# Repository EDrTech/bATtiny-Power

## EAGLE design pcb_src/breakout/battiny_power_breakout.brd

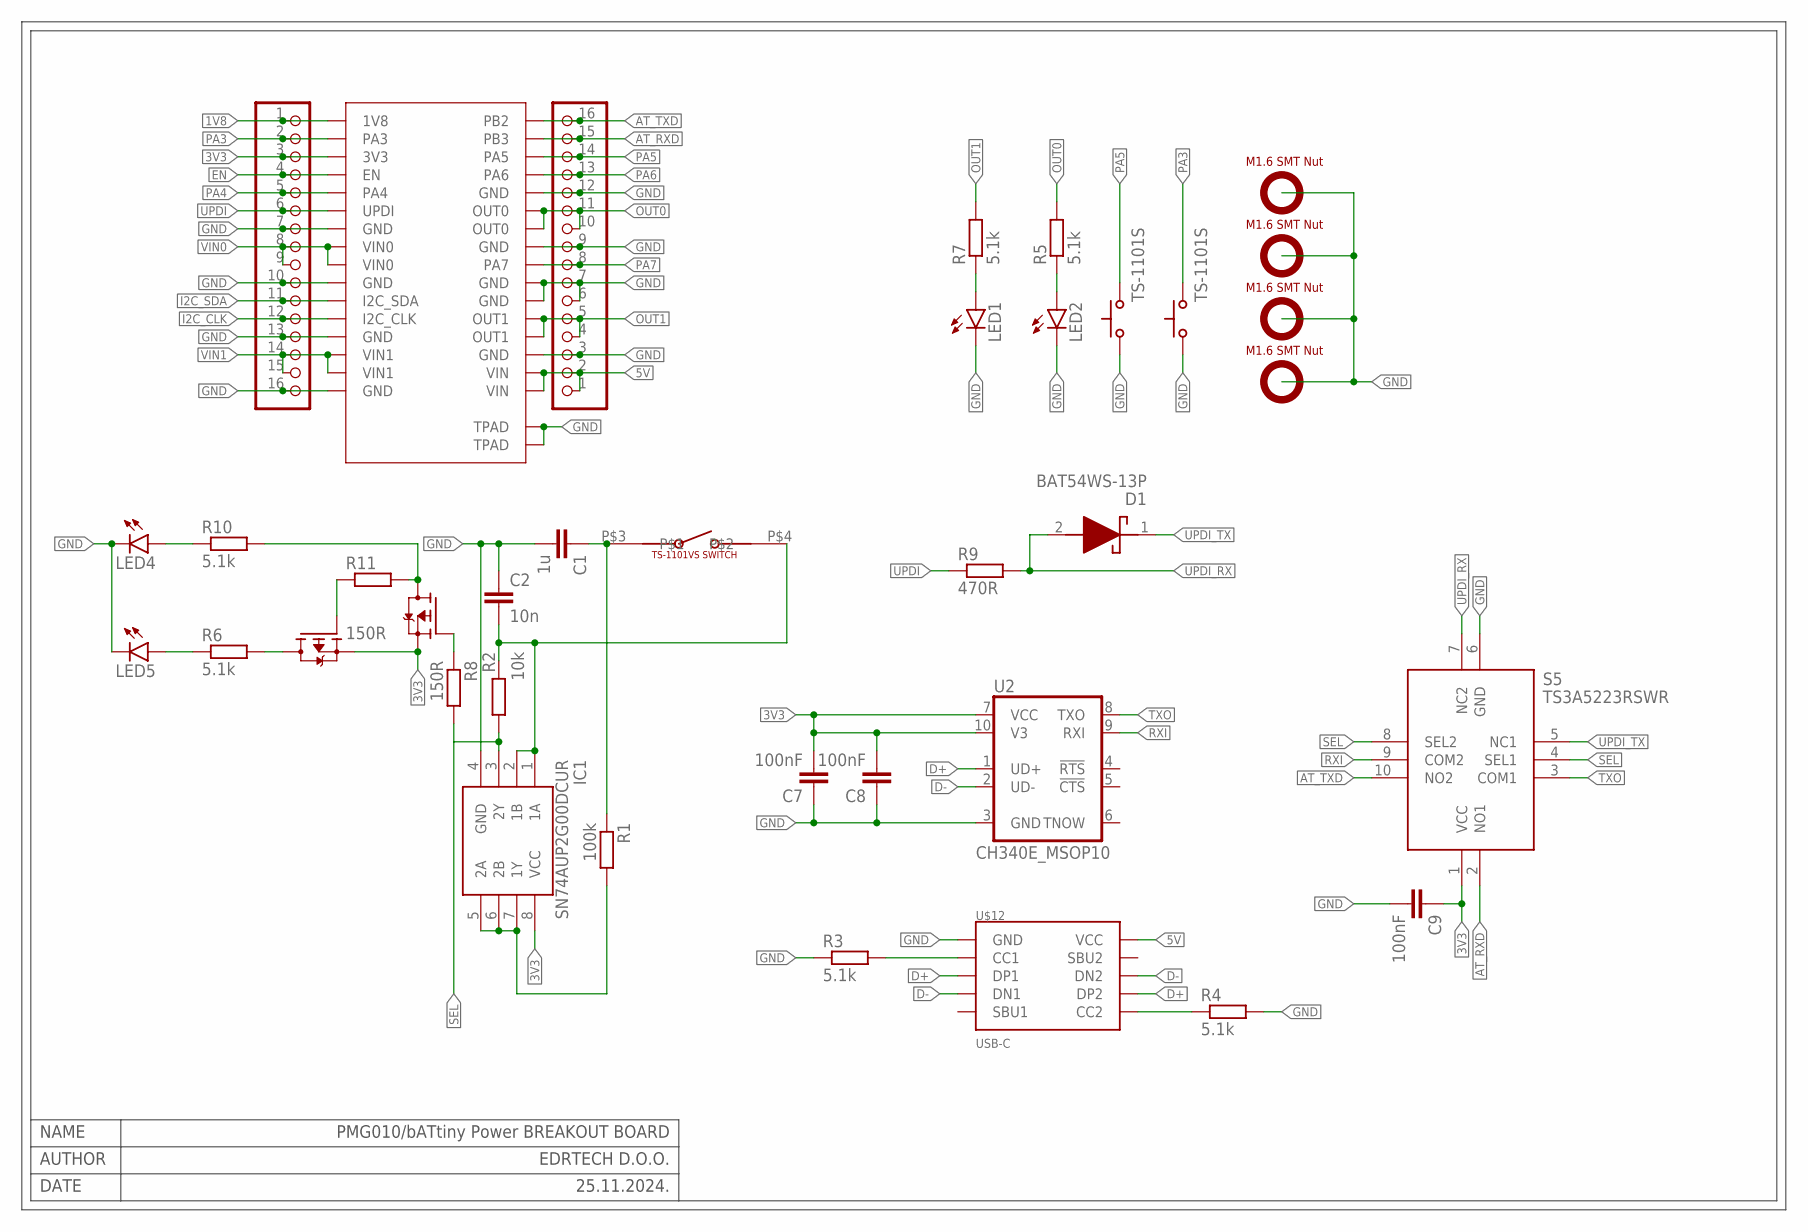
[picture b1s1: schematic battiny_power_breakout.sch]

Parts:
C1: 1u; C0402
C2: 10n; C0402
C7, C8, C9: 100nF; C0402
D1: BAT54WS-13P; SOD2512X115N
IC1: SN74AUP2G00DCUR; SOP50P310X90-8N
JP1, JP2: PINHD-1X16; 1X16
LED1, LED2, LED4, LED5: LEDCHIP-LED0603; CHIP-LED0603
Q1, Q2: NTK3139PT1G; SOTFL40P120X55-3N
R1: 100k; R0402
R2: 10k; R0402
R3, R4, R5, R6, R7, R10: 5.1k; R0402
R8, R11: 150R; R0402
R9: 470R; R0402
S5: TS3A5223RSWR; RSW(RPUQFNN10)
U2: CH340E_MSOP10; MSOP10
U$1, U$4: TS-1101S
U$2: TS-1101VS-C-A-A
U$3: PMG010
U$8, U$9, U$10, U$11: SMTSO16
U$12: USB-C

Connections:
1V8: JP1.1, U$3.P$1 (1V8)
3V3: C7.2, C8.2, C9.1, IC1.8 (VCC), JP1.3, Q1.2 (S), Q2.2 (S), S5.1 (VCC), U2.7 (VCC), U2.10 (V3), U$3.P$3 (3V3)
5V: JP2.1, JP2.2, U$3.P$17 (VIN), U$3.P$18 (VIN), U$12.VCC@1 (VCC), U$12.VCC@2 (VCC)
AT_RXD: JP2.15, S5.2 (NO1), U$3.P$31 (PB3)
AT_TXD: JP2.16, S5.10 (NO2), U$3.P$32 (PB2)
D+: U2.1 (UD+), U$12.DP1, U$12.DP2
D-: U2.2 (UD-), U$12.DN1, U$12.DN2
EN: JP1.4, U$3.P$4 (EN)
GND: C1.2, C2.1, C7.1, C8.1, C9.2, IC1.4 (GND), JP1.7, JP1.10, JP1.13, JP1.16, JP2.3, JP2.6, JP2.7, JP2.9, JP2.12, LED1.C, LED2.C, LED4.C, LED5.C, R3.1, R4.2, S5.6 (GND), U2.3 (GND), U$1.P$1 (1), U$3.P$7 (GND), U$3.P$10 (GND), U$3.P$13 (GND), U$3.P$16 (GND), U$3.P$19 (GND), U$3.P$22 (GND), U$3.P$23 (GND), U$3.P$25 (GND), U$3.P$28 (GND), U$3.P$33 (TPAD), U$3.P$34 (TPAD), U$4.P$1 (1), U$8.P$1, U$9.P$1, U$10.P$1, U$11.P$1, U$12.GND@1 (GND), U$12.GND@2 (GND), U$12.P$1 (GND), U$12.P$2 (GND), U$12.P$3 (GND), U$12.P$4 (GND)
I2C_CLK: JP1.12, U$3.P$12 (I2C_CLK)
I2C_SDA: JP1.11, U$3.P$11 (I2C_SDA)
unnamed: C2.2, IC1.1 (1A), IC1.2 (1B), R2.1, U$2.P$4
unnamed: R3.2, U$12.CC1
unnamed: LED2.A, R5.1
unnamed: LED5.A, R6.1
unnamed: Q1.1 (G), R8.1
unnamed: R4.1, U$12.CC2
unnamed: IC1.5 (2A), IC1.6 (2B), IC1.7 (1Y), R1.2
unnamed: Q1.3 (D), R10.2, R11.2
unnamed: Q2.3 (D), R6.2
unnamed: LED4.A, R10.1
unnamed: C1.1, R1.1, U$2.P$3
unnamed: Q2.1 (G), R11.1
unnamed: LED1.A, R7.1
OUT0: JP2.10, JP2.11, R5.2, U$3.P$26 (OUT0), U$3.P$27 (OUT0)
OUT1: JP2.4, JP2.5, R7.2, U$3.P$20 (OUT1), U$3.P$21 (OUT1)
PA3: JP1.2, U$3.P$2 (PA3), U$4.P$2 (2)
PA4: JP1.5, U$3.P$5 (PA4)
PA5: JP2.14, U$1.P$2 (2), U$3.P$30 (PA5)
PA6: JP2.13, U$3.P$29 (PA6)
PA7: JP2.8, U$3.P$24 (PA7)
RXI: S5.9 (COM2), U2.9 (RXI)
SEL: IC1.3 (2Y), R2.2, R8.2, S5.4 (SEL1), S5.8 (SEL2)
TXO: S5.3 (COM1), U2.8 (TXO)
UPDI: JP1.6, R9.1, U$3.P$6 (UPDI)
UPDI_RX: D1.2 (A), R9.2, S5.7 (NC2)
UPDI_TX: D1.1 (K), S5.5 (NC1)
VIN0: JP1.8, JP1.9, U$3.P$8 (VIN0), U$3.P$9 (VIN0)
VIN1: JP1.14, JP1.15, U$3.P$14 (VIN1), U$3.P$15 (VIN1)

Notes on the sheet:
PMG010/bATtiny Power BREAKOUT BOARD
NAME
AUTHOR
DATE
EDRTECH D.O.O.
25.11.2024.

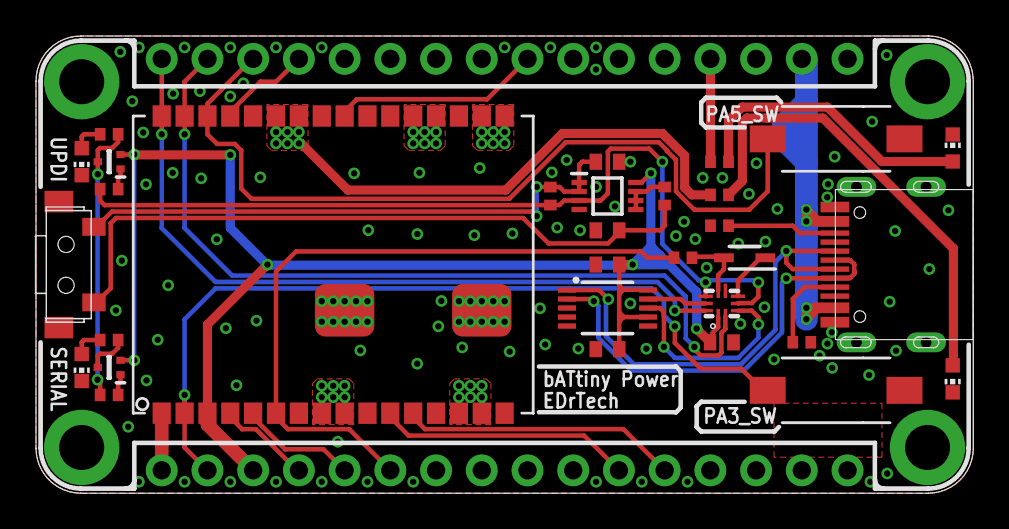
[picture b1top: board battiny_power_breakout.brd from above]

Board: 2 copper layers, 52.1 x 25.4 mm, 37 parts (0 on the bottom side), 39 nets.

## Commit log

2024-11-25 Repository created
2024-11-27 Updated, added BOM
